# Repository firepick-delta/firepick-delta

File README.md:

### FirePick Delta Hardware/Mechanical Repo

#### Summary / Context

Design and Manufacturing Specifications for [FirePick Delta](http://delta.firepick.org).  If you're a developer wanting to help, the best way to do that is to join the [mailing list](https://groups.google.com/forum/#!forum/firepick) and start a line of communication there.  

This repo only contains the hardware (sch/pcb) and mechanical (3d) files for FirePick Delta.  It inherits software from OpenPnP, Marlin, and FirePick.  Other repo's of interest for FirePick Delta:

* https://github.com/firepick-delta/openpnp
* https://github.com/firepick-delta/Marlin
* https://github.com/firepick1/FireREST
* https://github.com/firepick1/FireBOM

#### Mechanical Assembly Parts Tree, Instructions, and BOM

Please click the link below to navigate the mechanical assembly with our FireBOM wiki documentation system:

[AFPD0001](AFPD0001) FirePick Delta Hacker-Developer Edition

#### Licensing

These files are licensed under [*Creative Commons Attribution-ShareAlike (CC BY-SA)*](https://creativecommons.org/licenses/by-sa/4.0/legalcode).  Commercial use is OK, but you are required under the license conditions to share your changes with the internet, and also credit the FirePick Delta team.

This license lets others remix, tweak, and build upon your work even for commercial purposes, as long as they credit you and license their new creations under the identical terms. This license is often compared to “copyleft” free and open source software licenses. All new works based on yours will carry the same license, so any derivatives will also allow commercial use. This is the license used by Wikipedia, and is recommended for materials that would benefit from incorporating content from Wikipedia and similarly licensed projects. 

[View License Deed](http://creativecommons.org/licenses/by-sa/4.0/) | [View Legal Code](https://creativecommons.org/licenses/by-sa/4.0/legalcode)

#### Contributors
* [@FlyingLotus1983 (Neil Jansen)](https://github.com/FlyingLotus1983)
* [@firepick1 (Karl Lew)](https://github.com/firepick1)
* [@ChristianLerche (Christian Lerche)](https://github.com/ChristianLerche)
* [@daytonpid (Dayton Pidhirney)](https://github.com/daytonpid)
* [@codedetail (Dave Shanklin)](https://github.com/codedetail)
* [@obnauticus (Thomas Kilbride)](https://github.com/obnauticus)
* [@mstegen (Mike Stegen)](https://github.com/mstegen)
* [@mikeanton (Mike Anton)](https://github.com/mikeanton)

#### Maintainers
* [@FlyingLotus1983 (Neil Jansen)](https://github.com/FlyingLotus1983)
* [@firepick1 (Karl Lew)](https://github.com/firepick1)

#### Contributions and Pull Requests

If you'd like to contribute anything back to this repo, please do so via [pull requests](https://help.github.com/articles/using-pull-requests).  

Keep in mind that the Cubify Design files are binary blobs.  Assembly (AD_ASM) files contain filepath links back to dependent solid parts (AD_PRT), and parts contain filepath links back to the assembly.  This makes it extremely tricky to use version control.  You can't just rename files all willy-nilly, or else Cubify will get very angry.  Please excercise caution and contact the FirePick Delta Dev Team via [google group mailing list](https://groups.google.com/forum/#!forum/firepick) before attempting to modify anything of significant nature.

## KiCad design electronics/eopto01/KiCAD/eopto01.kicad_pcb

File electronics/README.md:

### Electronic Design Directory

To add a new circuit design, first choose a new ID:

* **E** is the ID prefix for electronic parts (e.g., [ECAM01](../../../wiki/ECAM01)).

Archive your new design in git:

1. `git checkout dev`
1. Create a new directory (e.g., **ecam01**) and add your design files
1. `git add --all`
1. `git commit -am "adding new PCB"`
1. `git fetch; git merge; git push`

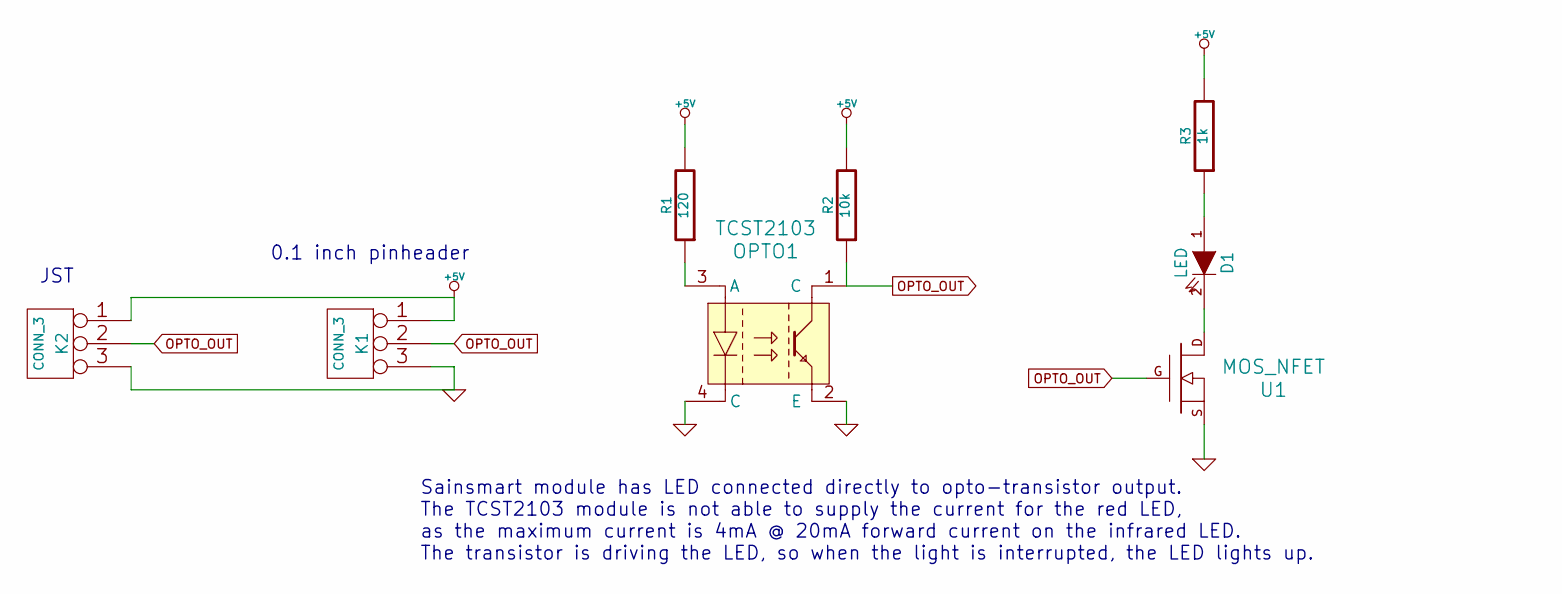
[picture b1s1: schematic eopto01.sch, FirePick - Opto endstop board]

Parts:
D1: LED
K1, K2: CONN_3
OPTO1: TCST2103
R1: 120
R2: 10k
R3: 1k
U1: MOS_NFET

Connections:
+5V: K1.1, K2.1, R1.2, R2.2, R3.2
GND: K1.3, K2.3, OPTO1.2 (E), OPTO1.4 (C), U1.2 (S)
unnamed: D1.1 (A), R3.1
unnamed: D1.2 (K), U1.3 (D)
unnamed: OPTO1.3 (A), R1.1
OPTO_OUT: K1.2 (PM), K2.2 (PM), OPTO1.1 (C), R2.1, U1.1 (G)

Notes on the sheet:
Sainsmart module has LED connected directly to opto-transistor output. The TCST2103 module is not able to supply the current for the red LED, as the maximum current is 4mA @ 20mA forward current on the infrared LED. The transistor is driving the LED, so when the light is interrupted, the LED lights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
JST
0.1 inch pinheader

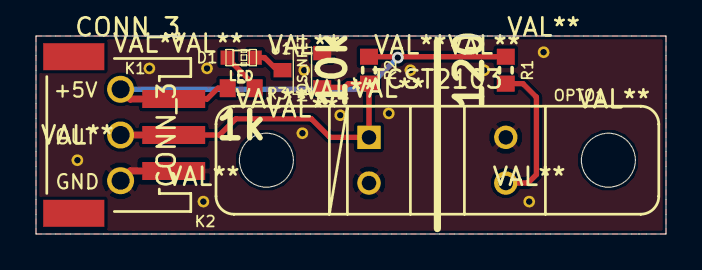
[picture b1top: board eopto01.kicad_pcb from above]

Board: 2 copper layers, 35.0 x 11.0 mm, 8 parts (0 on the bottom side), 6 nets.

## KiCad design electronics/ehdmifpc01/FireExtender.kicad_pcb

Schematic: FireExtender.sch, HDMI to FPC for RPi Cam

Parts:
C1, C2: 0.1uF
J1: HDMI_TYPE_A
J2: CONN_15_RPI-CAM

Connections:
/+3V3: C1.1, C2.1, J1.18, J2.15
/CLK+: J1.10, J2.11
/CLK-: J1.12, J2.12
/D0+: J1.7, J2.8
/D0-: J1.9, J2.9
/D1+: J1.4, J2.5
/D1-: J1.6, J2.6
/D2+: J1.1, J2.2
/D2-: J1.3, J2.3
/SCL: J1.15, J2.13
/SDA: J1.16, J2.14
GND: C1.2, C2.2, J1.2, J1.5, J1.8, J1.11, J1.17, J2.1, J2.4, J2.7, J2.10

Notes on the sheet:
HDMI to FPC connector for RPi CAM

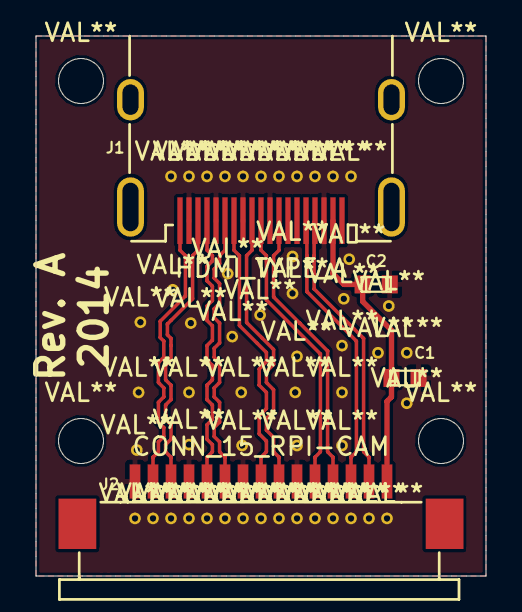
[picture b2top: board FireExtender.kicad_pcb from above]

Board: 2 copper layers, 25.0 x 30.0 mm, 4 parts (0 on the bottom side), 12 nets.

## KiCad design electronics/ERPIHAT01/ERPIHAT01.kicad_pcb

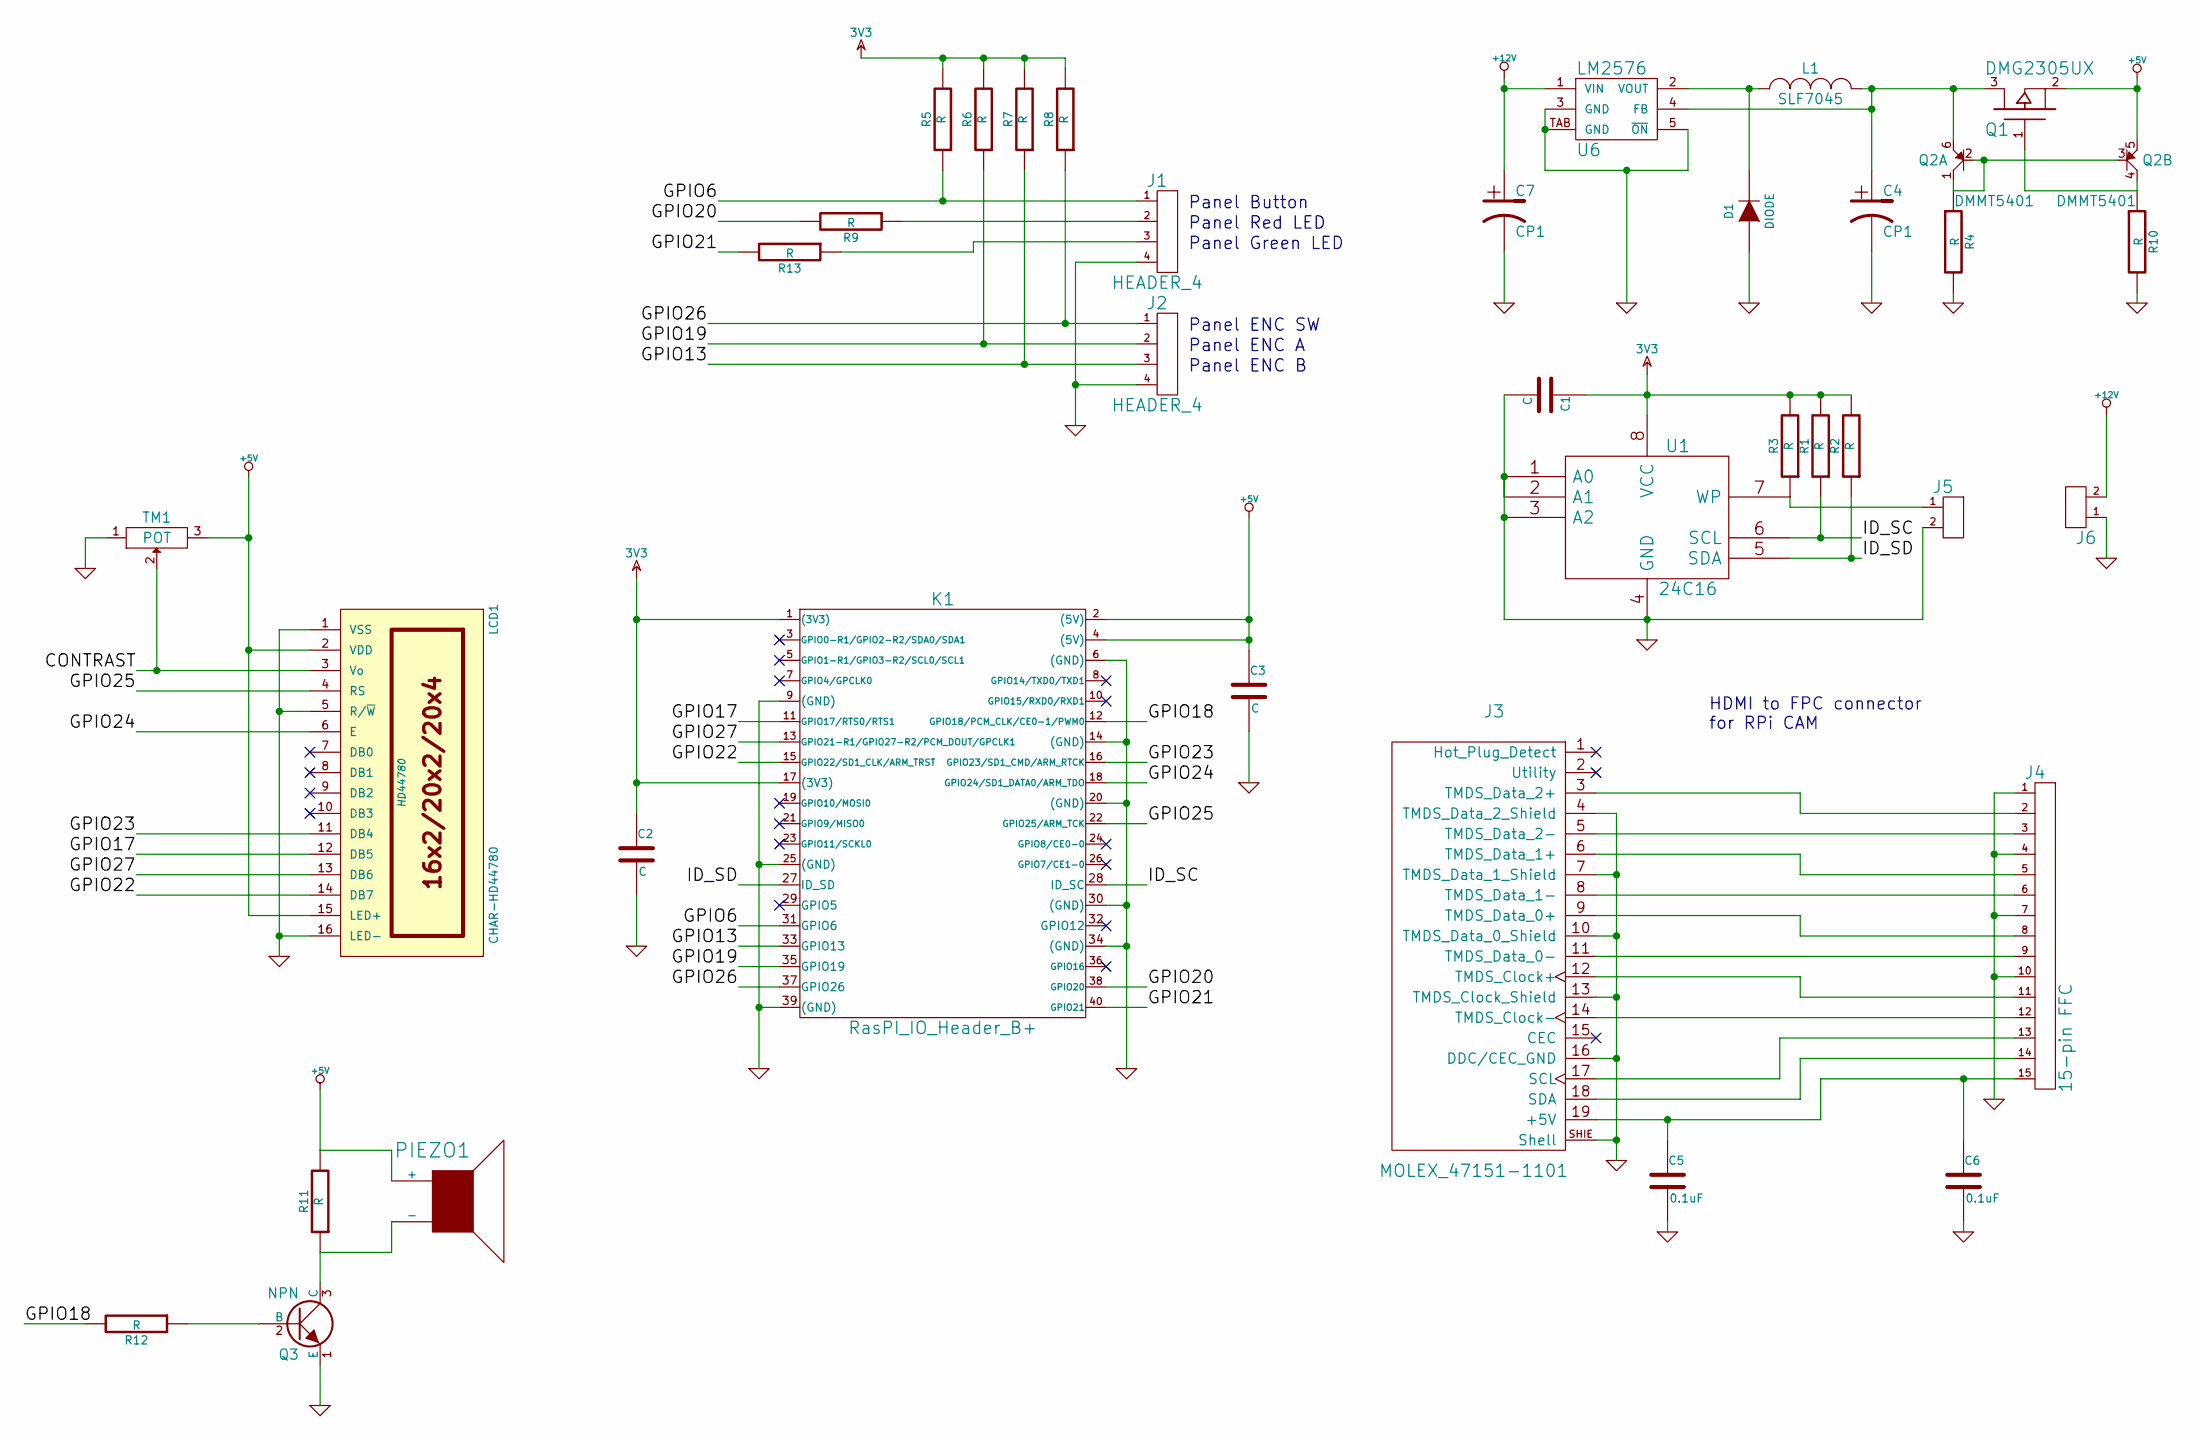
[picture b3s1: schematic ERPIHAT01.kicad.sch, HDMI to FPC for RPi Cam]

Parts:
C1, C2, C3: C
C4, C7: CP1
C5, C6: 0.1uF
D1: DIODE
J1, J2: HEADER_4
J3: MOLEX_47151-1101
J4: 15-pin FFC
J5, J6: HEADER_2
K1: RasPI_IO_Header_B+
L1: SLF7045
LCD1: CHAR-HD44780; HD44780
PIEZO1: SPEAKER
Q1: DMG2305UX
Q2: DMMT5401
Q3: NPN
R1, R2, R3, R4, R5, R6, R7, R8, R9, R10, R11, R12, R13: R
TM1: POT
U1: 24C16
U6: LM2576

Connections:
3V3: C1.1, C2.1, K1.1 ((3V3)), K1.17 ((3V3)), R1.2, R2.2, R3.2, R5.2, R6.2, R7.2, R8.2, U1.8 (VCC)
+5V: C3.1, K1.2 ((5V)), K1.4 ((5V)), LCD1.2 (VDD), LCD1.15 (LED+), PIEZO1.+, Q1.2 (S), Q2.5 (E), R11.2, TM1.3
+12V: C7.+, J6.2, U6.1 (VIN)
/CONTRAST: LCD1.3 (Vo), TM1.2
/GPIO6: J1.1, K1.31 (GPIO6), R5.1
/GPIO13: J2.3, K1.33 (GPIO13), R7.1
/GPIO17: K1.11 (GPIO17/RTS0/RTS1), LCD1.12 (DB5)
/GPIO18: K1.12 (GPIO18/PCM_CLK/CE0-1/PWM0), R12.2
/GPIO19: J2.2, K1.35 (GPIO19), R6.1
/GPIO20: K1.38 (GPIO20), R9.2
/GPIO21: K1.40 (GPIO21), R13.2
/GPIO22: K1.15 (GPIO22/SD1_CLK/ARM_TRST), LCD1.14 (DB7)
/GPIO23: K1.16 (GPIO23/SD1_CMD/ARM_RTCK), LCD1.11 (DB4)
/GPIO24: K1.18 (GPIO24/SD1_DATA0/ARM_TDO), LCD1.6 (E)
/GPIO25: K1.22 (GPIO25/ARM_TCK), LCD1.4 (RS)
/GPIO26: J2.1, K1.37 (GPIO26), R8.1
/GPIO27: K1.13 (GPIO21-R1/GPIO27-R2/PCM_DOUT/GPCLK1), LCD1.13 (DB6)
/ID_SC: K1.28 (ID_SC), R1.1, U1.6 (SCL)
/ID_SD: K1.27 (ID_SD), R2.1, U1.5 (SDA)
GND: C1.2, C2.2, C3.2, C4.-, C5.2, C6.2, C7.-, D1.A, J1.4, J2.4, J3.4 (TMDS_Data_2_Shield), J3.7 (TMDS_Data_1_Shield), J3.10 (TMDS_Data_0_Shield), J3.13 (TMDS_Clock_Shield), J3.16 (DDC/CEC_GND), J3.SHIE (Shell), J4.1, J4.4, J4.7, J4.10, J5.2, J6.1, K1.6 ((GND)), K1.9 ((GND)), K1.14 ((GND)), K1.20 ((GND)), K1.25 ((GND)), K1.30 ((GND)), K1.34 ((GND)), K1.39 ((GND)), LCD1.1 (VSS), LCD1.5 (R/~W), LCD1.16 (LED-), Q3.1 (E), R4.2, R10.2, TM1.1, U1.1 (A0), U1.2 (A1), U1.3 (A2), U1.4 (GND), U6.3 (GND), U6.5 (~ON), U6.TAB (GND)
unnamed: C4.+, L1.2, Q1.3 (D), Q2.6 (E), U6.4 (FB)
unnamed: C5.1, C6.1, J3.19 (+5V), J4.15
unnamed: D1.C (K), L1.1, U6.2 (VOUT)
unnamed: J1.2, R9.1
unnamed: J1.3, R13.1
unnamed: J3.3 (TMDS_Data_2+), J4.2
unnamed: J3.5 (TMDS_Data_2-), J4.3
unnamed: J3.6 (TMDS_Data_1+), J4.5
unnamed: J3.8 (TMDS_Data_1-), J4.6
unnamed: J3.9 (TMDS_Data_0+), J4.8
unnamed: J3.11 (TMDS_Data_0-), J4.9
unnamed: J3.12 (TMDS_Clock+), J4.11
unnamed: J3.14 (TMDS_Clock-), J4.12
unnamed: J3.17 (SCL), J4.13
unnamed: J3.18 (SDA), J4.14
unnamed: J5.1, R3.1, U1.7 (WP)
unnamed: PIEZO1.-, Q3.3 (C), R11.1
unnamed: Q1.1 (G), Q2.4 (C), R10.1
unnamed: Q2.1 (C), Q2.2 (B), Q2.3 (B), R4.1
unnamed: Q3.2 (B), R12.1

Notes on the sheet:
HDMI to FPC connector for RPi CAM
Panel Button
Panel Red LED
Panel Green LED
Panel ENC SW
Panel ENC A
Panel ENC B

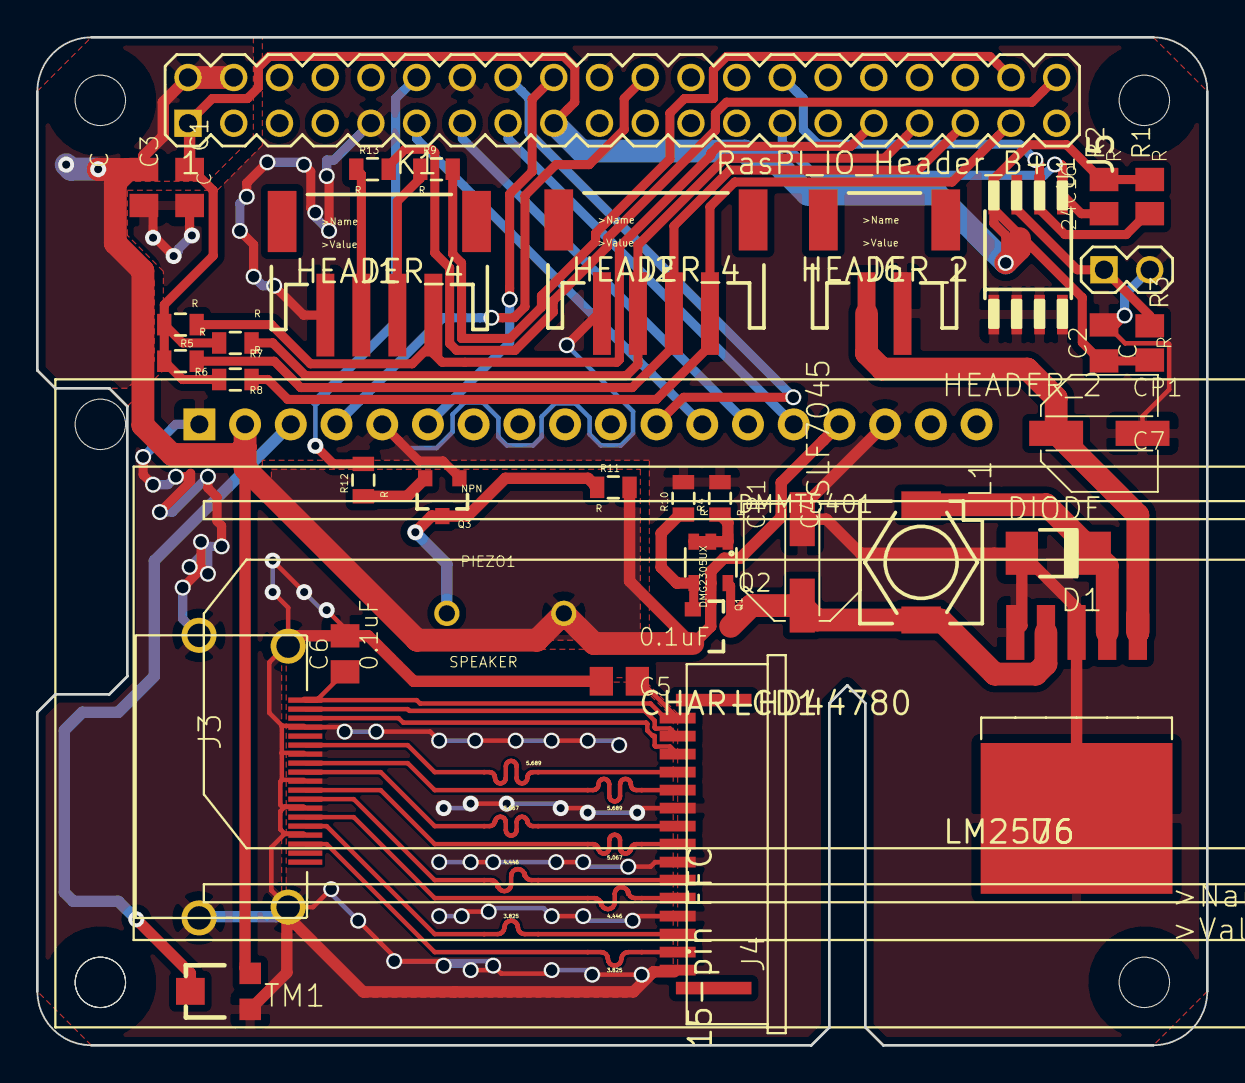
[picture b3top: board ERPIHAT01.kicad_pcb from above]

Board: 2 copper layers, 65.0 x 56.0 mm, 49 parts (0 on the bottom side), 40 nets.

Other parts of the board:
3.825, 3.825#2, 4.446, 4.446#2, 5.067, 5.067#2, 5.689, 5.689#2: VAL**; MuSelf
@HOLE0, @HOLE1, @HOLE2, @HOLE3: (no value)

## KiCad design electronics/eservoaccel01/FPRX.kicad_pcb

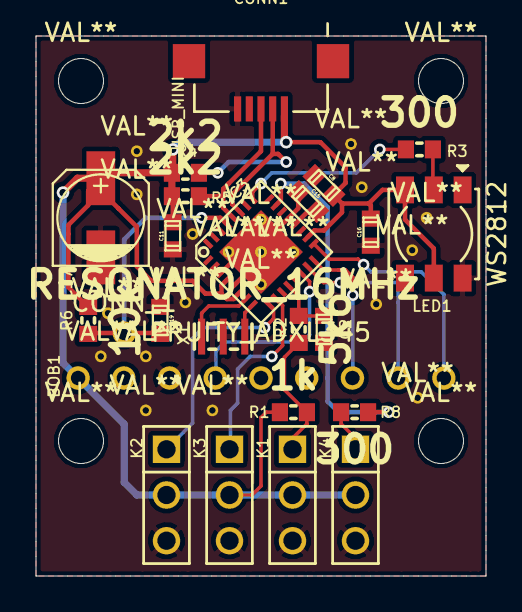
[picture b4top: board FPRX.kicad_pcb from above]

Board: 2 copper layers, 25.0 x 30.0 mm, 23 parts (0 on the bottom side), 20 nets.

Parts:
BOB1: FRUITY_ADXL345; Lerche_9P_2.54mm
C2, C8, C11, C15, C16, C19: 0.1uF; c_0603
C17: 100uF; c_elec_5x5.8
CONN1: USB_MINI; Lerche_Sparkfun_MicroUSB
IC3: ATMEGA328P-M; QFN32-5x5
K1, K2, K3, K4: CONN_3; PIN_ARRAY_3X1
LED1: WS2812; Lerche_WS2812
R1: 1k; Lerche_R0603
R2: 5k6; Lerche_R0603
R3, R8: 300; Lerche_R0603
R4, R5: 2k2; Lerche_R0603
R6: 10k; Lerche_R0603
X1: RESONATOR_16MHz; Lerche_CSTCE_G_Resonator

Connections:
+5V: BOB1.1, C8.1, C11.1, C16.1, C17.1, CONN1.1, IC3.4, IC3.6, IC3.18, K1.2, K2.2, K3.2, K4.2, LED1.3, LED1.5, R1.1, R4.1, R5.1, R6.1
DOUT_STATUS: IC3.25, R3.1
GND: BOB1.3, C2.2, C8.2, C11.2, C15.2, C16.2, C17.2, C19.2, CONN1.5, IC3.3, IC3.5, IC3.21, IC3.33, K1.3, K2.3, K3.3, K4.3, LED1.6, X1.2
MISO: BOB1.7, IC3.16
MOSI: BOB1.8, IC3.15
unnamed: K1.1, R1.2, R2.2
unnamed: IC3.23, R8.1
unnamed: LED1.2, R3.2
unnamed: C15.1, IC3.20
unnamed: IC3.8, X1.3
unnamed: IC3.7, X1.1
SCK: BOB1.9, IC3.17
SCL: CONN1.3, IC3.28, R5.2
SDA: CONN1.2, IC3.27, R4.2
Servo1: IC3.9, K2.1
Servo2: IC3.10, K3.1
WS-DIN: K4.1, R8.2
ZPROBE: C2.1, IC3.12, R2.1
~RESET: C19.1, IC3.29, R6.2
~SS: BOB1.4, IC3.14

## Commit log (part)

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2014-06-12 initial
2014-06-13 adding new PCB
2014-06-13 updating PCB
2014-06-13 updating PCB and adding GERBERS+BOM
2014-06-13 Fixed silkscreen and updated gerbers to final rev
2014-06-16 Rev. A for RS485 to Servo and Accelerometer
2014-06-17 Rev. A PCB HDMI to FPC converter, for RPi Cam
2014-06-17 Removed unused components from schematic, added WS2812 LED, changed C18 to C17
2014-06-17 Added components reference to silkscreen
2014-06-17 Added title to worksheet for SCH, added image of PCB and PDF of schematic
2014-06-17 Added schematic PDF and image of PCB
2014-06-17 Added reference for C11 & C12
2014-06-18 Added resistor for WS2812 onboard LED, connected to the right input
2014-06-18 Differential traces are length matched now
2014-06-23 New chip and layout + A axis motor controller/Board still not finalized
2014-06-23 adding new PDF
2014-06-23 adding new unfinished PCB
2014-06-24 adding some used libraries
2014-06-24 updated pinouts
2014-06-24 Added modular tool connectors, RasPi connector, Front Panel connector. 
2014-06-24 Fixed File
2014-06-24 no edit
2014-06-24 recover lost changes
2014-06-24 Revert "recover lost changes"
    This reverts commit 0ce016bf4596014ad1f4ff05d6638003136b1386.
2014-06-24 Restore Neil's changes 1d1a
2014-06-24 adding Dayton's 5958 ICSP/Power circuits to Neil's board
2014-06-24 rename with dashes
2014-06-24 Fixed schematics
    looks more uniform
2014-06-24 New Library
2014-06-24 Added FFC connector from HDMI
2014-06-24 Fixed errors/connectors
    Fixed the ERC errors, ones that are left just ignore. Neil needs to add
    his library of proper JST connectors to the board and we will be pretty
    much ready to route.
2014-06-24 added updated PDF
2014-06-25 Adding new FirePick-approved library
2014-06-25 Added connectors for prototype FirePick Delta motion controller board Rev.1
2014-06-26 Added pcb outline for FPC-EMC01-1284.brd, and placed connectors per AutoCAD DXF. Added male 16-pin connector to firepick.lbr.
2014-06-26 Moved stepper driver IC's to symmetrically-pleasing locations
2014-06-26 minor tweaks before layout
2014-06-26 Routed J15-J1
2014-07-02 Update README.md
    added links to other important repos
2014-07-04 Changed connector on LCD board. Added notes to EMC01 board.
2014-07-06 Wired up encoder, switches, and LEDs
2014-07-07 Redesigned with Micro USB instead of Microfit. PCB is now smaller. Using I2C to communicate with motion controller
2014-07-09 modifying gitignore to ignore temp vim files
2014-07-11 adding bom markdown generation scripts, testing FireBOM URL /github path
2014-07-11 moving BOM to firepick-delta.wiki
2014-07-11 KiCAD version of the opto-endstop. Adding transistor for LED
2014-07-11 Forgot how to Eagle, but added DC/DC. Change components for better specs
2014-07-12 Added JST connector for Opto-endstop
2014-07-14 Added StepStick to library, and updated EMC01 schematic/pcb
2014-07-15 fixing I2C connectors, adding FTDI, adding sch for motor controllers
2014-07-15 Changed to Sparkfun Micro USB connector
2014-07-17 board partially routed
2014-07-17 emc01 routing update
2014-07-18 polygonception
2014-07-18 routing update
2014-07-26 deleting directory '3d'
2014-07-28 some extra routing
2014-07-30 Adding mechanical parts
2014-07-30 adding dummy files so to create empty directories
2014-07-30 adding creative commons CC-BY-SA license to mechanical files
2014-07-31 - Added FPD main assembly AFPD0001 - FirePick Delta Hacker-Developer Edition.AD_ASM - Connected carbon rod delta linkages
2014-07-31 Adding STL's for 3d printed files
2014-07-31 added jigs/fixtures, adding component feeder mount assembly
2014-08-01 Adding 2D prints and DXF's for acrylic frame plates
2014-08-01 New end effector stuff
2014-08-01 updating top-level README.md to include creative-commons png and other useful info
2014-08-01 adding fasteners to frame, still playing with end effector cam/hdmi board
2014-08-01 Finished adding T-nuts to frame
2014-08-01 Fixing issue where Cubify was bitching about problems encountered while loading AD0001 - Frame.AD_ASM
2014-08-02 Adding feeder mounts to AFPD0001 - FirePick Delta Hacker-Developer Edition.AD_ASM
2014-08-02 Adding pretty things to EMC01.AD_ASM
2014-08-02 Adding stuff for SMT nozzle, and checking in some stuff that I somehow missed
2014-08-02 Moved EMC01 to assembly
2014-08-02 Importing Raspberry Pi STL model downloaded from: http://www.inti-innovations.co.uk/products/inti-media/inti-media-raspberrypi.html
2014-08-03 Created RasPi HAT for camera pass-through and LCD/buttons. Prettied up RasPi Model B+ model.
2014-08-12 Changed power connector from 3-pin to 2-pin
2014-08-13 - Swapped FT232RL for FT231XS (copied/pasted to Sparkfun RedBoard) - Replaced micro USB with mini USB - Deleted second micro USB and Z probe pin (we can use a modular connector Z probe instead rather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
2014-08-14 Adding lots of new SMT component feeders and stuff!
2014-08-14 Fixed 608 bearing block nut trap clearance Fixed bottom plate, added clearance slots for Misumi diagonal braces, which have alignment tabs.
2014-08-14 Updated 608 bearing block STL and bottom plate DXF after making fixes from last commit
2014-08-18 FPD parts
    Brackets and Plates
2014-08-18 corner bracket
2014-08-18 3D0051.stl
2014-08-18 Transcribed Eagle schematic to KiCAD with some minor, mostly asthetic changes and added RPi GPIOs for the encoder, buttons and LEDs. Imported Christian's HDMItoFFC adapter for the PiCam.
2014-08-18 Imported the Eagle board file to KiCAD. Found a place for everthing. Switched places between the power JST and the encoder JST. Routed everything. Matched trace lengths for HDMI to FFC PiCam adapter.
2014-08-18 3D0051
2014-08-18 3D0051.stl.zip
2014-08-18 STL as binary
2014-08-21 3D0456-final-draft
2014-08-25 saving intermediate
2014-08-25 constraints
2014-08-26 autorouting v1
2014-08-26 autorouting v2 w/ groundplane
2014-08-27 constraints (really)
2014-08-27 plated updated cubify model
2014-08-28 Changed to correct pinout for Type A HDMI
2014-08-28 PushPlastics orange 3mm PLA @ 220C/60-50C TAZ4. 2.5hrs
2014-08-30 Loose Fit for delta drive parts
2014-09-02 Cleaned up EMC01 board and finalized for peer review
2014-09-03 Cleaned up ERPIHAT01 board and finalized for peer review
2014-09-03 Cleanups after peer review
2014-09-03 Forgot some labels
2014-09-04 Print tested TAZ.
2014-09-04 Fixed minor issues and changed modular tool connector pinout to allow better routing of GND and +12V planes
2014-09-07 Updated EAGLE library for firepick-specific stuff
2014-09-07 Updated all EAGLE PCB's for first Prototype production run.
2014-09-07 cleanup
2014-09-09 REVISION A of EMC01 board. Fixed unconnected wires on TOOL1_ENABLE, TOOL2_ENABLE, TOOL3_ENABLE, and TOOL4_ENABLE. This was discovered by Seeed Studio Fusion PCB service after being submitted to be ma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
2014-09-10 RasPiCam wrench; 3mm effector rod holes
2014-09-10 Moved wrench to Jigs and renamed to fit Neil's numbering
2014-09-10 Forgot STL
2014-09-10 LC Hook
2014-09-10 Renamed to remove extra zero
2014-09-10 More zeros
2014-09-11 Legacy HW mounts (Mega, RPi B)
2014-09-12 Mirror plate. A calibration hunch. Let's see where it goes...
2014-09-12 Mirror plate calibration hunch
2014-09-24 Minor tweaks
2014-09-24 Cleaned up in NetFabb
2014-09-24 Merged in STL fix for 3D0051 from dev-loose
2014-09-26 Changed to MOSFET for LED
2014-10-01 adding new PCB rev
2014-10-02 Revision A, after assembling first batch of PCBs.
2014-10-05 Added link to FireBOM AFPD0001 page
2014-10-06 adding list of contributors and maintainers
2014-10-08 * New Ball-stud delta rods * Updates for new PCB assemblies * Updates for LCD bezel assembly * Updates for modular tools * Other misc stuff
2014-10-08 Adding LCD bezel, fixing corner brackets
2014-10-10 Updated delta mechanism, feeders. Added magnetic bed.
2014-10-10 Updating all STLs
2014-10-10 updating markdown with new contributers :)
2014-10-10 Sproing
2014-10-12 more cool stuff
2014-10-12 Updating feeder design... seems somewhat usable now :-/
2014-10-22 Continuing work on feeders, cameras, and other misc mechanical pieces
2014-10-23 Full Rod
2014-10-23 Added a chopped up version of the top plate that you can print on a Taz sized 3d printer.
2014-10-24 Improved blender file to make it more procedural. The meshes intended for export are now laregely made with modifiers.
2014-10-24 Moved hole on corner. Removed fluff. Its now threads into the center of the vertical extrusion just like the rubber feet. Generated with the improved blender file, and ended up removing unnecessary f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
2014-10-24 Enlarged holes to 5.5 mm to fit M5 bolts. Oops All holes to attatch to the frame are additionally positioned using modifiers now, to change the size (or shape for that matter) of each hole, you only 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
2014-10-25 Loose version
2014-10-27 Ball stud changes
2014-10-27 3D spring for 3D0234 delta effector rod
2014-10-27 Delta rod spring
2014-10-29 New MCU Conversion
    AT90 is hooked up in schematic
2014-10-30 adding .gcode to .gitignore
2014-10-30 Added CONN-OSTTA020161 to Firepick.lbr
2014-10-30 EMC01 Revision B: Added +5V voltage regulator and other misc stuff
2014-10-30 *.l** added
2014-10-30 Updating PDFs for Rev B EMC01
2014-10-30 Updates to EAT0001 (Rev. A)
2014-10-30 Adding new files. Assembly isn't usable, just checking in before merge...
2014-10-31 minor cosmetic and refdes updates
2014-11-01 Pi wedge
2014-11-01 Wedge prototype
2014-11-02 Camera hacks
2014-11-04 RPiCam mount
2014-11-04 M2Nut Trap
2014-11-04 Nut trap, broken assembly
2014-11-05 Plate
2014-11-05 Tweak
2014-11-06 Sizing
2014-11-06 Effector STL
2014-11-06 Minor tweaks for usability
2014-11-08 split notch
2014-11-09 Eliminate catenary spring rattle by reducing hole size
2014-11-10 Modify bearing block to accept Nylock nuts
    Also adds a bit of strength to stop nut tearing it's mounting out.
2014-11-10 Rename
2014-11-10 Revert "Modify bearing block to accept Nyloc nuts"
2014-11-12 Better catenary springs
2014-11-12 Vacuum coupling; ROM mods for rods
2014-11-13 N8 mount
2014-11-14 README
2014-11-14 image
2014-11-14 Nema8
2014-11-14 LC1005
2014-11-14 LC1005 -> 3DLC10005
2014-11-16 Extrusion washer; Vacuum shaft coupling
2014-11-18 3DLC0456
2014-11-18 3DLC0454
2014-11-19 3D plates
2014-11-20 Tubing Tool and End Cap
2014-11-20 PC04; Hack cleanup
2014-11-20 PC04
2014-11-20 M8 removal
2014-11-20 DXF for Igor
2014-11-21 T Handle
2014-11-21 Delta arm with shaft
2014-11-22 3DLC0002
2014-11-22 3DLC0051A
2014-11-23 Limit switch interruptor
2014-11-23 limit
2014-11-23 Arm collision fix
2014-11-24 Print support
2014-11-27 Effector plate
2014-11-27 Vertical print
2014-11-28 bearing lbock
2014-11-30 STEP and SAT files
2014-11-30 STEP file conversion
2014-12-11 work
2015-04-04 updating STLs
2015-04-04 deleted
2015-04-11 added brim and fixed bridging issue
2015-04-13 reverting back to 9991c084dfd11b766cb2ae2e9ac17f71bdc60d1a
2015-05-06 Checkin of mostly-production-ready files
2015-05-06 Removing STL's from mechanical (moving them to 'production files' dir)
2015-05-06 baleted
2015-05-06 Moving STL's over here
2015-05-06 Initial check-in of the packing list for FPD beta kits
2015-05-06 new boards,
2015-05-06 forgot to check you in
2015-05-08 Fixed frame mounting screw hole. Reverting back to M5 hardware from M3X which didn't work as expected... The M3X needs more work before it can be re-introduced.
2015-05-08 Adding new stuff!
2015-05-14 new stuff, checking in before bay area trip
2015-06-03 Adding schematic and fabrication drawing PDFs
2015-06-04 Updated the EMC02 schematic PDF to include the second page
2015-06-13 Revised Laser Tool
    -Updated to laser heat sink with built in protection in the laser head.
    -Added more fins around area where fans blow air
    -Renamed files to suit convention
    -Added PCB Assemblies
    -Added Eagle files
2015-06-13 Gernerated pdf files
2015-06-29 Laser Schematic + PCB Update
    Added 30 mm fan mounts + connector
    Changed values to suit mods on prototype
    Added switchmode PSU enable line to global enable line to stop current
    flowing
    Added more TODO:'s to schematic
    Added copper pours on both sides of PCB
2015-07-11 Further schematic updates
    - updated comments on schematic
    - added credit to crow + license terms
    - generated pdf's
